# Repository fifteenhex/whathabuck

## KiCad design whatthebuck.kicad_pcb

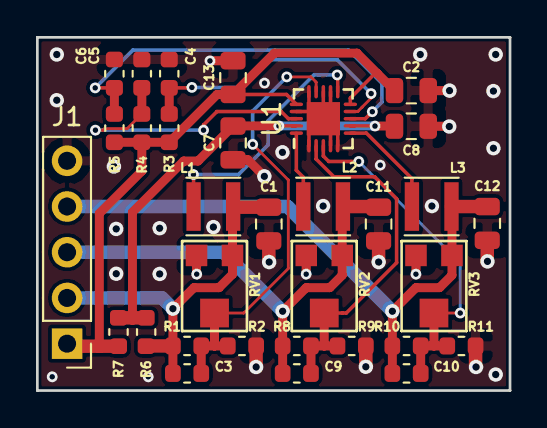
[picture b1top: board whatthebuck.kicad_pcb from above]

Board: 2 copper layers, 26.3 x 19.6 mm, 32 parts (0 on the bottom side), 15 nets.

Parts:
C1, C2, C7, C8, C11, C12, C13: C; C_0805_2012Metric
C3, C4, C5, C6, C9, C10: C; C_0603_1608Metric
J1: Conn_01x05; PinHeader_1x05_P2.54mm_Vertical
L1, L2, L3: L; L_Taiyo-Yuden_MD-3030
R1, R2, R3, R4, R5, R6, R7, R8, R9, R10, R11: R; R_0603_1608Metric
RV1, RV2, RV3: R_POT; 3x3pot
U1: ea3036c; UQFN-20-1EP_3x3mm_P0.4mm_EP1.85x1.85mm

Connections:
+1V0: C9.1, C11.1, J1.3, L2.2, R8.1, RV2.1
+1V8: C10.1, C12.1, J1.4, L3.2, R10.1, RV3.1
+3V3: C1.1, C3.1, J1.2, L1.1, R1.1, R6.1, RV1.1
GND: C1.2, C2.2, C4.2, C5.2, C6.2, C7.2, C8.2, C11.2, C12.2, C13.2, J1.5, R2.2, R9.2, R11.2, RV1.3, RV2.3, RV3.3, U1.1, U1.4, U1.5, U1.12, U1.13, U1.15, U1.17, U1.21
unnamed: C3.2, R1.2, R2.1, RV1.2, U1.14
unnamed: C4.1, R3.2, U1.9
unnamed: C5.1, R4.2, U1.18
unnamed: C6.1, R5.2, U1.8
unnamed: C7.1, C8.1, R6.2, R7.2, U1.7, U1.19
unnamed: C9.2, R8.2, R9.1, RV2.2, U1.2
unnamed: C10.2, R10.2, R11.1, RV3.2, U1.3
unnamed: L1.2, U1.11
unnamed: L2.1, U1.20
unnamed: L3.1, U1.6
VCC: C2.1, C13.1, J1.1, R3.1, R4.1, R5.1, R7.1, U1.10, U1.16

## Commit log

2019-04-10 rev0
2020-06-13 Add fp/syn lib-table files
    By having those files, the footprint and symbol libraries are
    automatically imported as a project specific libs making everything
    working out of the box.
